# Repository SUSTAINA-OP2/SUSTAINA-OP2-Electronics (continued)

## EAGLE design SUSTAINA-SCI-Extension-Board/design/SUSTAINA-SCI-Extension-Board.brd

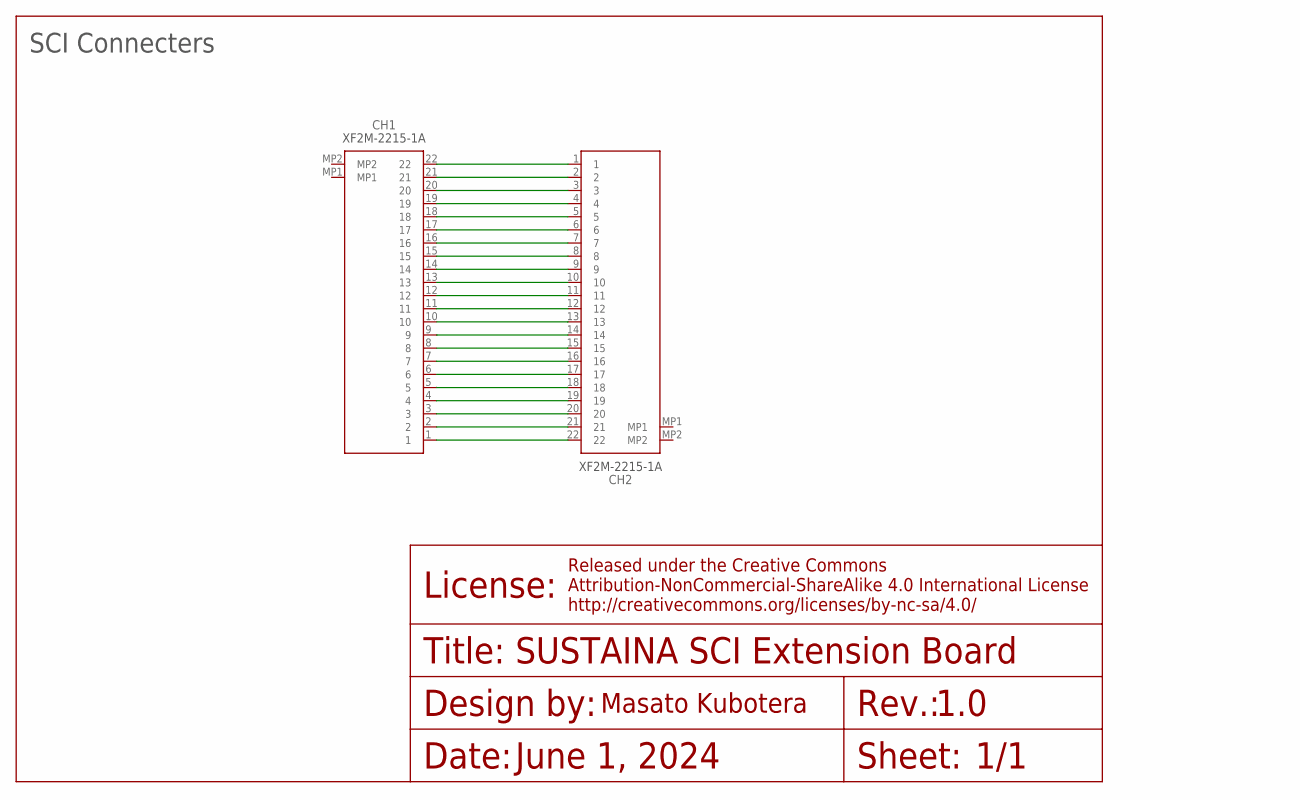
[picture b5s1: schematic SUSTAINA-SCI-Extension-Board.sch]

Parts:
CH1, CH2: XF2M-2215-1A

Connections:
unnamed: CH1.22, CH2.1
unnamed: CH1.21, CH2.2
unnamed: CH1.20, CH2.3
unnamed: CH1.19, CH2.4
unnamed: CH1.18, CH2.5
unnamed: CH1.17, CH2.6
unnamed: CH1.16, CH2.7
unnamed: CH1.15, CH2.8
unnamed: CH1.14, CH2.9
unnamed: CH1.13, CH2.10
unnamed: CH1.12, CH2.11
unnamed: CH1.11, CH2.12
unnamed: CH1.10, CH2.13
unnamed: CH1.9, CH2.14
unnamed: CH1.8, CH2.15
unnamed: CH1.7, CH2.16
unnamed: CH1.6, CH2.17
unnamed: CH1.5, CH2.18
unnamed: CH1.4, CH2.19
unnamed: CH1.2, CH2.21
unnamed: CH1.3, CH2.20
unnamed: CH1.1, CH2.22

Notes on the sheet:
June 1, 2024
SUSTAINA SCI Extension Board
1.0
1/1
SCI Connecters

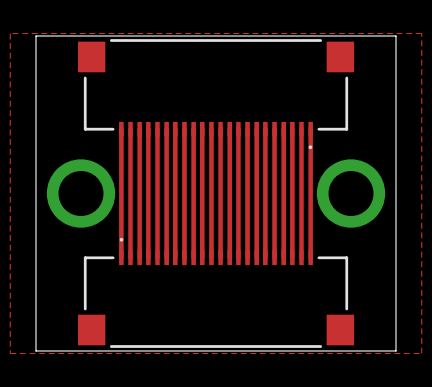
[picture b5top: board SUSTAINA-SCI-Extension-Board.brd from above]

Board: 2 copper layers, 20.0 x 17.5 mm, 4 parts (2 on the bottom side), 22 nets.

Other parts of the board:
U$1: SUSTAINA_SCI_EXTENSION_BOARD-0.03
U$2: DESIGNED_BY_MASATO_KUBOTERA_ON_JUNE_1-0.03

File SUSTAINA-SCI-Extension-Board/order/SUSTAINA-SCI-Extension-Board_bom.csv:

Comment,Designator,Footprint,LCSC Part #
XF2M-2215-1A,CH1 CH2,XF2M-2215-1A,C231416

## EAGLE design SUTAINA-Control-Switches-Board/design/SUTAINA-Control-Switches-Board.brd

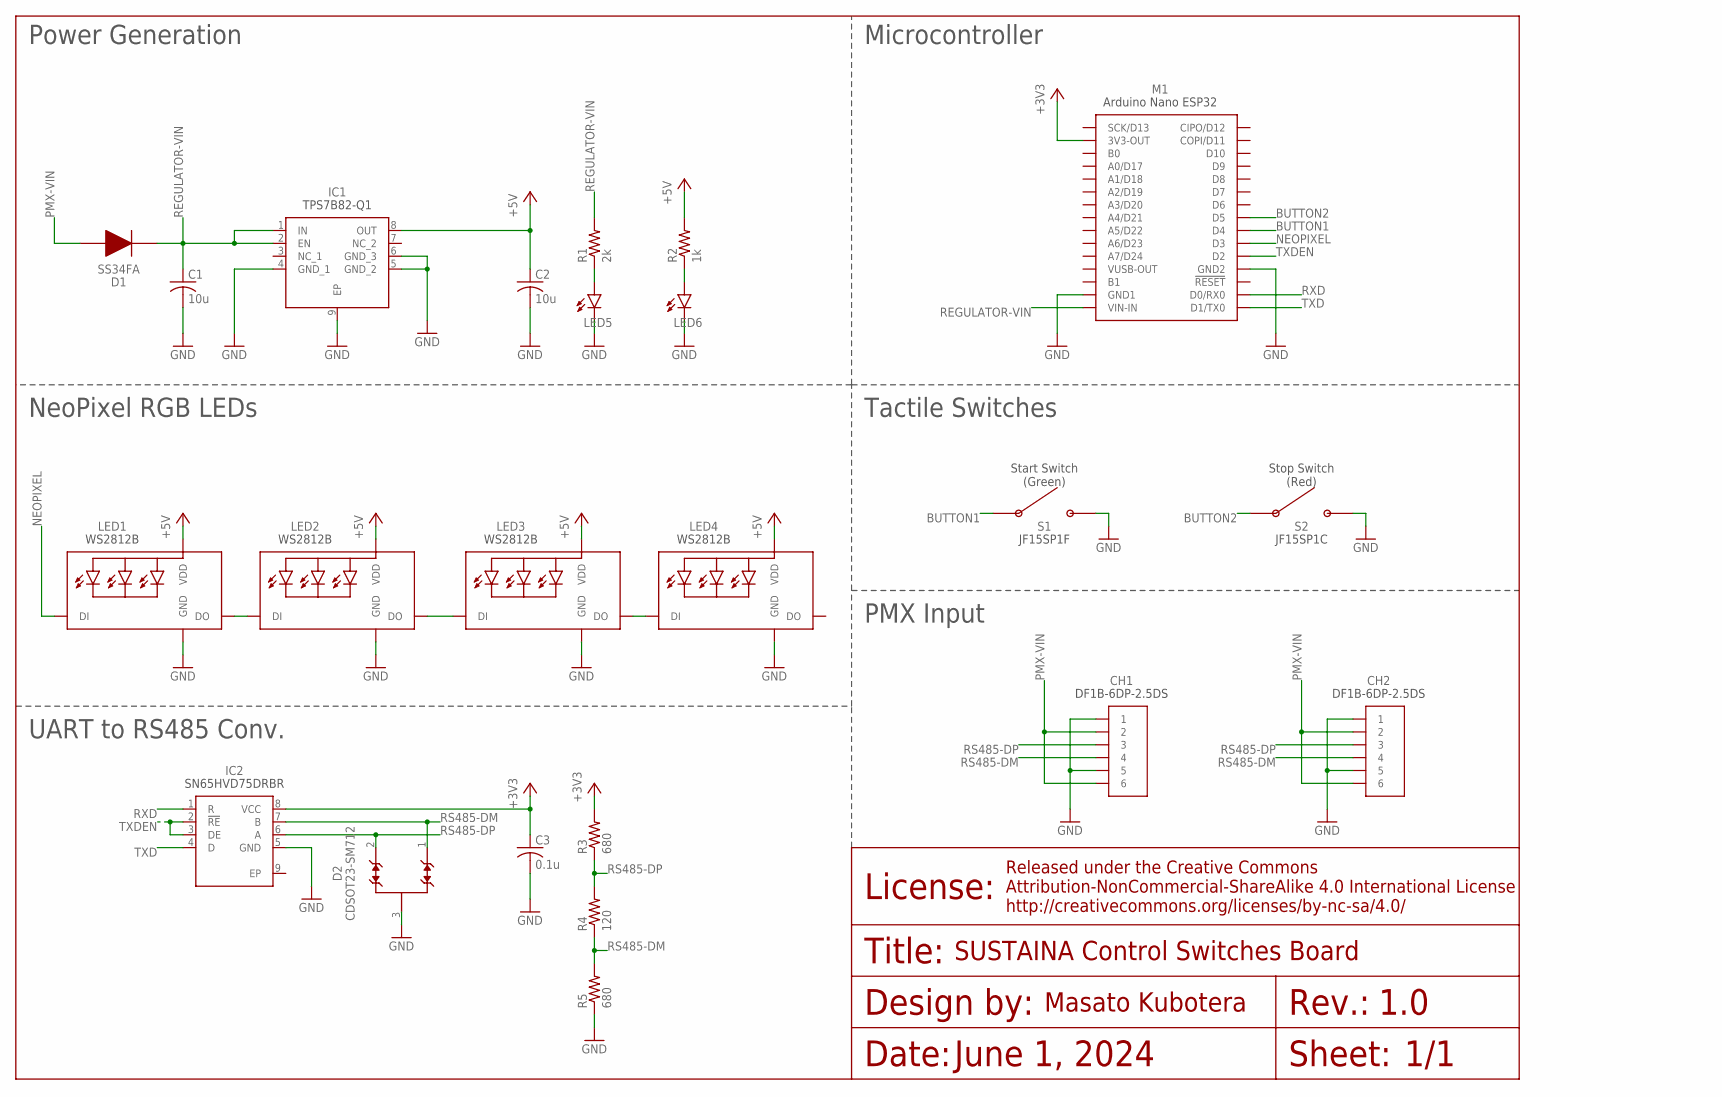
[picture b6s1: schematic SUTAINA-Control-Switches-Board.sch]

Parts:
C1, C2: 10u; C0603
C3: 0.1u; C0603
CH1, CH2: DF1B-6DP-2.5DS
D1: SS34FA
D2: CDSOT23-SM712; SOT-23-3
IC1: TPS7B82-Q1; SOP65P490X110-9N
IC2: SN65HVD75DRBR; SON65P300X300X100-9N
LED1, LED2, LED3, LED4: WS2812B
LED5, LED6: LEDSML0603; SML0603
M1: NANO-ESP32
R1: 2k; R0603
R2: 1k; R0603
R3, R5: 680; R0603
R4: 120; R0603
S1: JF15SP1F; JF15SP1
S2: JF15SP1C; JF15SP1

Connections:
+3V3: C3.1, IC2.8 (VCC), M1.3V3-OUT, R3.2
+5V: C2.1, IC1.8 (OUT), LED1.1-VDD (VDD), LED2.1-VDD (VDD), LED3.1-VDD (VDD), LED4.1-VDD (VDD), R2.2
BUTTON1: M1.D4, S1.1, S1.2
BUTTON2: M1.D5, S2.1, S2.2
DO-DI-1: LED1.2-DOUT (DO), LED2.4-DIN (DI)
DO-DI-2: LED2.2-DOUT (DO), LED3.4-DIN (DI)
DO-DI-3: LED3.2-DOUT (DO), LED4.4-DIN (DI)
GND: C1.2, C2.2, C3.2, CH1.1, CH1.5, CH2.1, CH2.5, D2.3, IC1.4 (GND_1), IC1.5 (GND_2), IC1.6 (GND_3), IC1.9 (EP), IC2.5 (GND), LED1.3-GND (GND), LED2.3-GND (GND), LED3.3-GND (GND), LED4.3-GND (GND), LED5.C, LED6.C, M1.GND1, M1.GND2, R5.1, S1.3, S1.4, S2.3, S2.4
LED-D-RX: LED6.A, R2.1
LED-D-TX: LED5.A, R1.1
NEOPIXEL: LED1.4-DIN (DI), M1.D3
PMX-VIN: CH1.2, CH1.6, CH2.2, CH2.6, D1.2
REGULATOR-VIN: C1.1, D1.1, IC1.1 (IN), IC1.2 (EN), M1.VIN-IN, R1.2
RS485-DM: CH1.4, CH2.4, D2.1, IC2.7 (B), R4.1, R5.2
RS485-DP: CH1.3, CH2.3, D2.2, IC2.6 (A), R3.1, R4.2
RXD: IC2.1 (R), M1.D0/RX0
TXD: IC2.4 (D), M1.D1/TX0
TXDEN: IC2.2 (!RE), IC2.3 (DE), M1.D2

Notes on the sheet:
Start Switch (Green)
Stop Switch (Red)
Tactile Switches
1.0
1/1
June 1, 2024
SUSTAINA Control Switches Board
Power Generation
Microcontroller
NeoPixel RGB LEDs
PMX Input
UART to RS485 Conv.

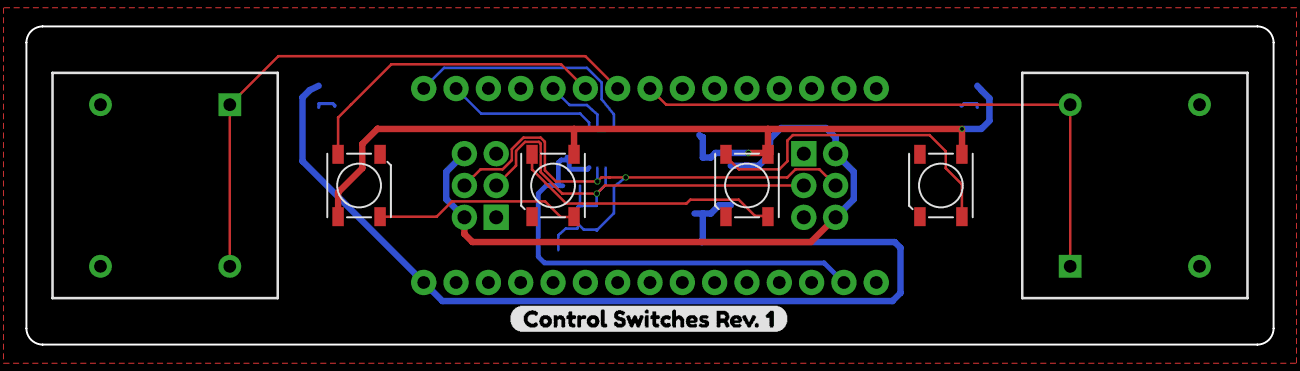
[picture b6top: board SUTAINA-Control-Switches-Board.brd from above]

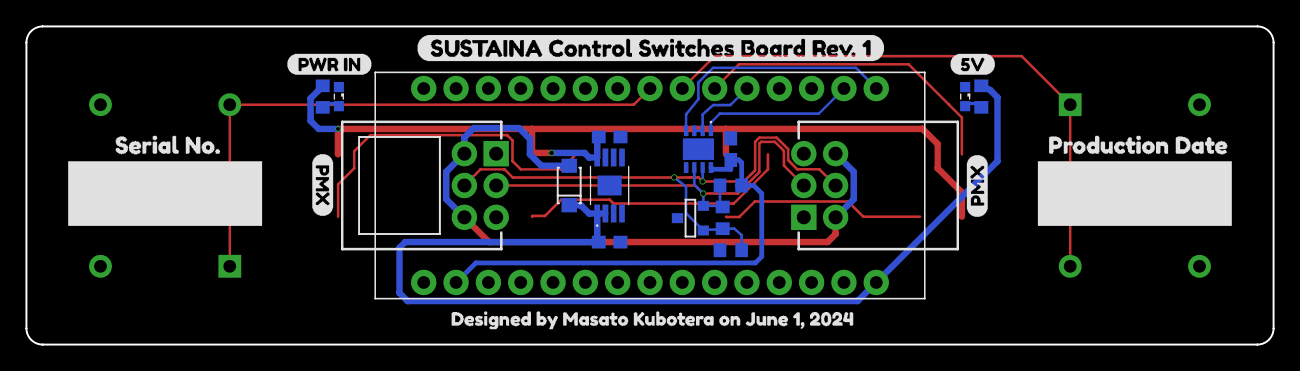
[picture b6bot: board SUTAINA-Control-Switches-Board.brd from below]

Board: 2 copper layers, 98.0 x 25.0 mm, 32 parts (25 on the bottom side), 18 nets.

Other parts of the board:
U$1: SUSTAINA_CONTROL_SWITCHES_BOARD_REV#_10
U$2, U$5: PMX0
U$3: PRODUCTION_DATE0
U$4: SERIAL_NO#0
U$6: CONTROL_SWITCHES_REV#_10
U$7: PWR_IN0
U$8: 5V
U$28: DESIGNED_BY_MASATO_KUBOTERA_ON_FEBRUARY_190DESIGN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; DESIGNED_BY_MASATO_KUBOTERA_ON_JUNE_1

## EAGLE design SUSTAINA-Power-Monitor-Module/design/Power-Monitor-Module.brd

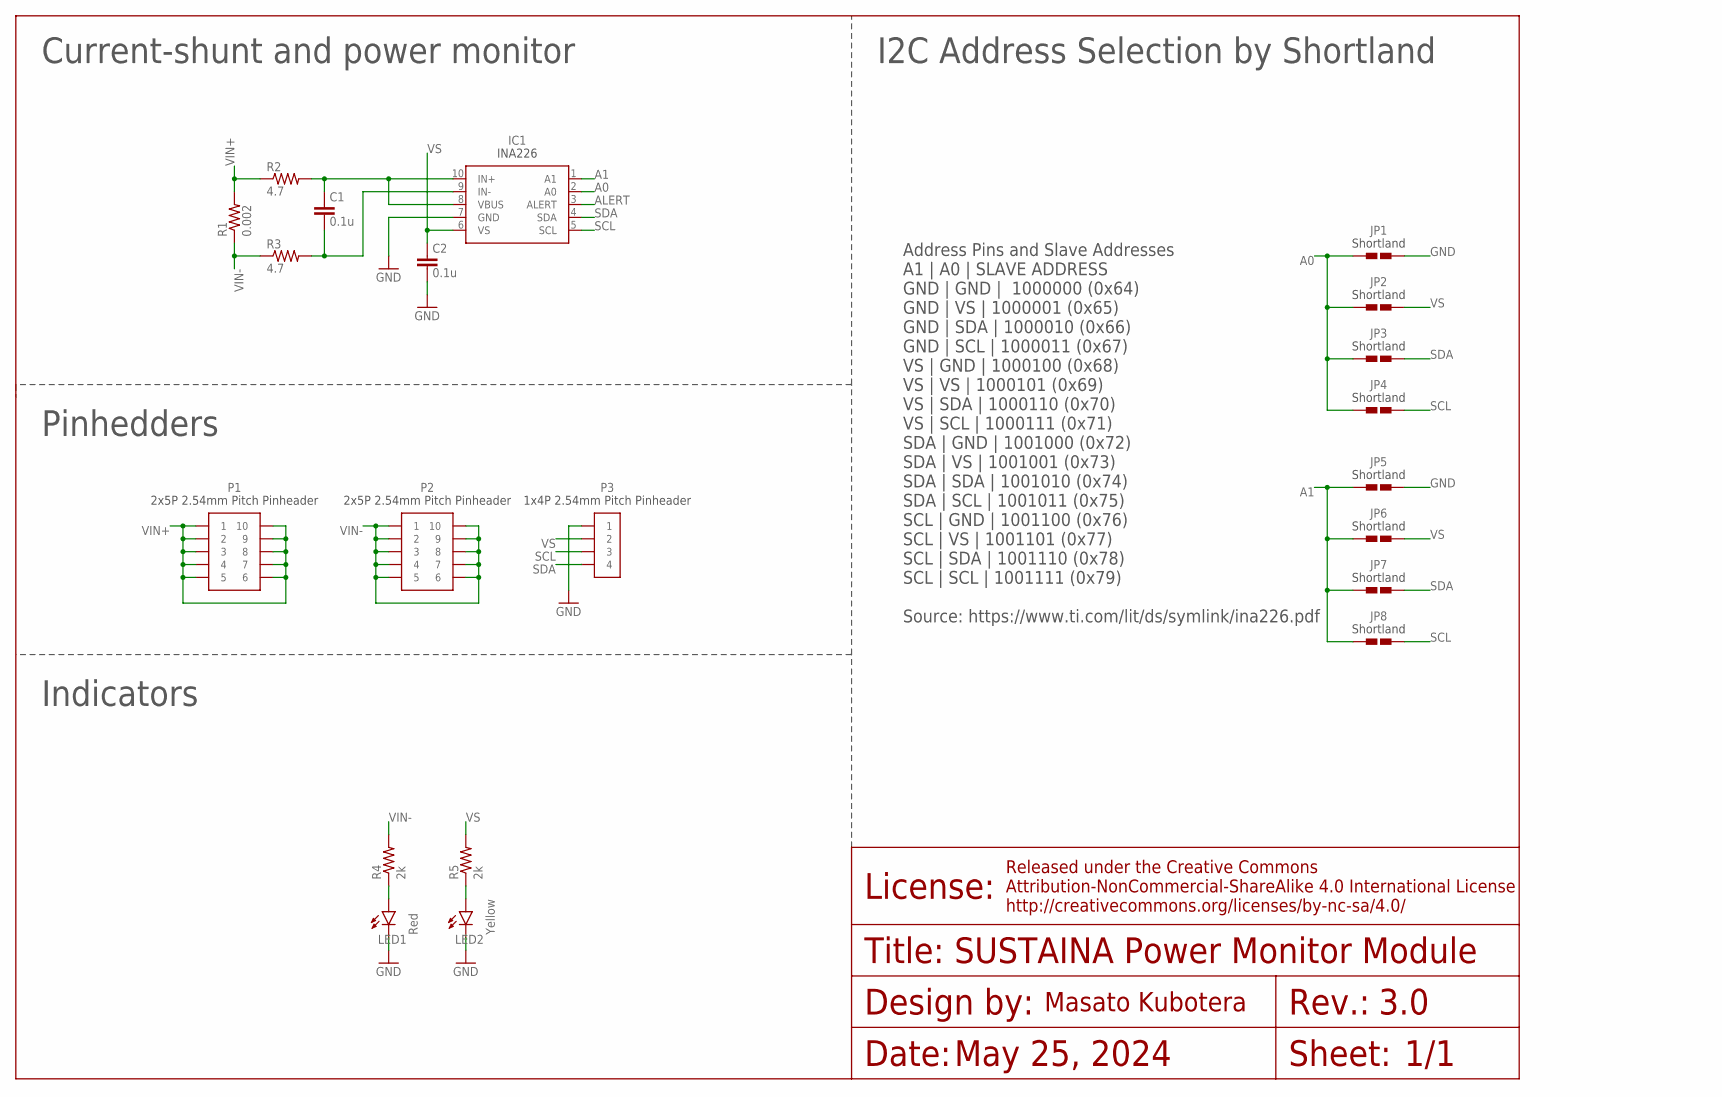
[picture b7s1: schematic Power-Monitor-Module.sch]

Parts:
C1, C2: 0.1u; C0402
IC1: INA226; MSOP-10
JP1, JP2, JP3, JP4, JP5, JP6, JP7, JP8: SHORTLAND
LED1: Red; SML0603
LED2: Yellow; SML0603
P1, P2: 2X5P
P3: 1X4P
R1: 0.002; R2512
R2, R3: 4.7; R0402
R4, R5: 2k; R0402

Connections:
A0: IC1.2 (A0), JP1.1, JP2.1, JP3.1, JP4.1
A1: IC1.1 (A1), JP5.1, JP6.1, JP7.1, JP8.1
ALERT: IC1.3 (ALERT)
GND: C2.2, IC1.7 (GND), JP1.2, JP5.2, LED1.C, LED2.C, P3.1
IN+: C1.1, IC1.8 (VBUS), IC1.10 (IN+), R2.2
IN-: C1.2, IC1.9 (IN-), R3.2
LED1_: LED1.A, R4.1
LED2: LED2.A, R5.1
SCL: IC1.5 (SCL), JP4.2, JP8.2, P3.3
SDA: IC1.4 (SDA), JP3.2, JP7.2, P3.4
VIN+: P1.1, P1.2, P1.3, P1.4, P1.5, P1.6, P1.7, P1.8, P1.9, P1.10, R1.2, R2.1
VIN-: P2.1, P2.2, P2.3, P2.4, P2.5, P2.6, P2.7, P2.8, P2.9, P2.10, R1.1, R3.1, R4.2
VS: C2.1, IC1.6 (VS), JP2.2, JP6.2, P3.2, R5.2

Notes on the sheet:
I2C Address Selection by Shortland
Pinhedders
Current-shunt and power monitor
May 25, 2024
SUSTAINA Power Monitor Module
3.0
1/1
Address Pins and Slave Addresses A1 | A0 | SLAVE ADDRESS GND | GND | 1000000 (0x64) GND | VS | 1000001 (0x65) GND | SDA | 1000010 (0x66) GND | SCL | 1000011 (0x67) VS | GND | 1000100 (0x68) VS | VS | 1000101 (0x69) VS | SDA | 1000110 (0x70) VS | SCL | 1000111 (0x71) SDA | GND | 1001000 (0x72) SDA |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
Indicators

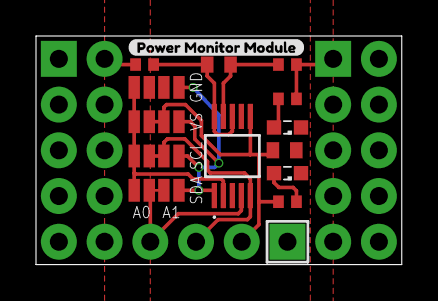
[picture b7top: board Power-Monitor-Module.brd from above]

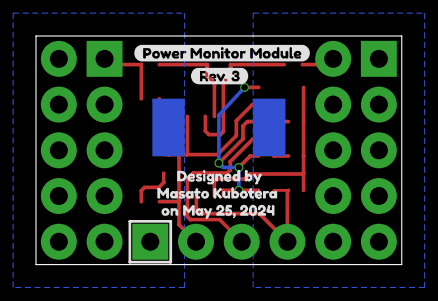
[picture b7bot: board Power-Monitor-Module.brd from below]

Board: 2 copper layers, 20.3 x 12.7 mm, 25 parts (4 on the bottom side), 12 nets.

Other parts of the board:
U$1, U$2: POWER_MONITOR_MODULE
U$3: REV#_3
U$5: DESIGNED_BY_MASATO_KUBOTERA_ON_MAY_25-0.0225

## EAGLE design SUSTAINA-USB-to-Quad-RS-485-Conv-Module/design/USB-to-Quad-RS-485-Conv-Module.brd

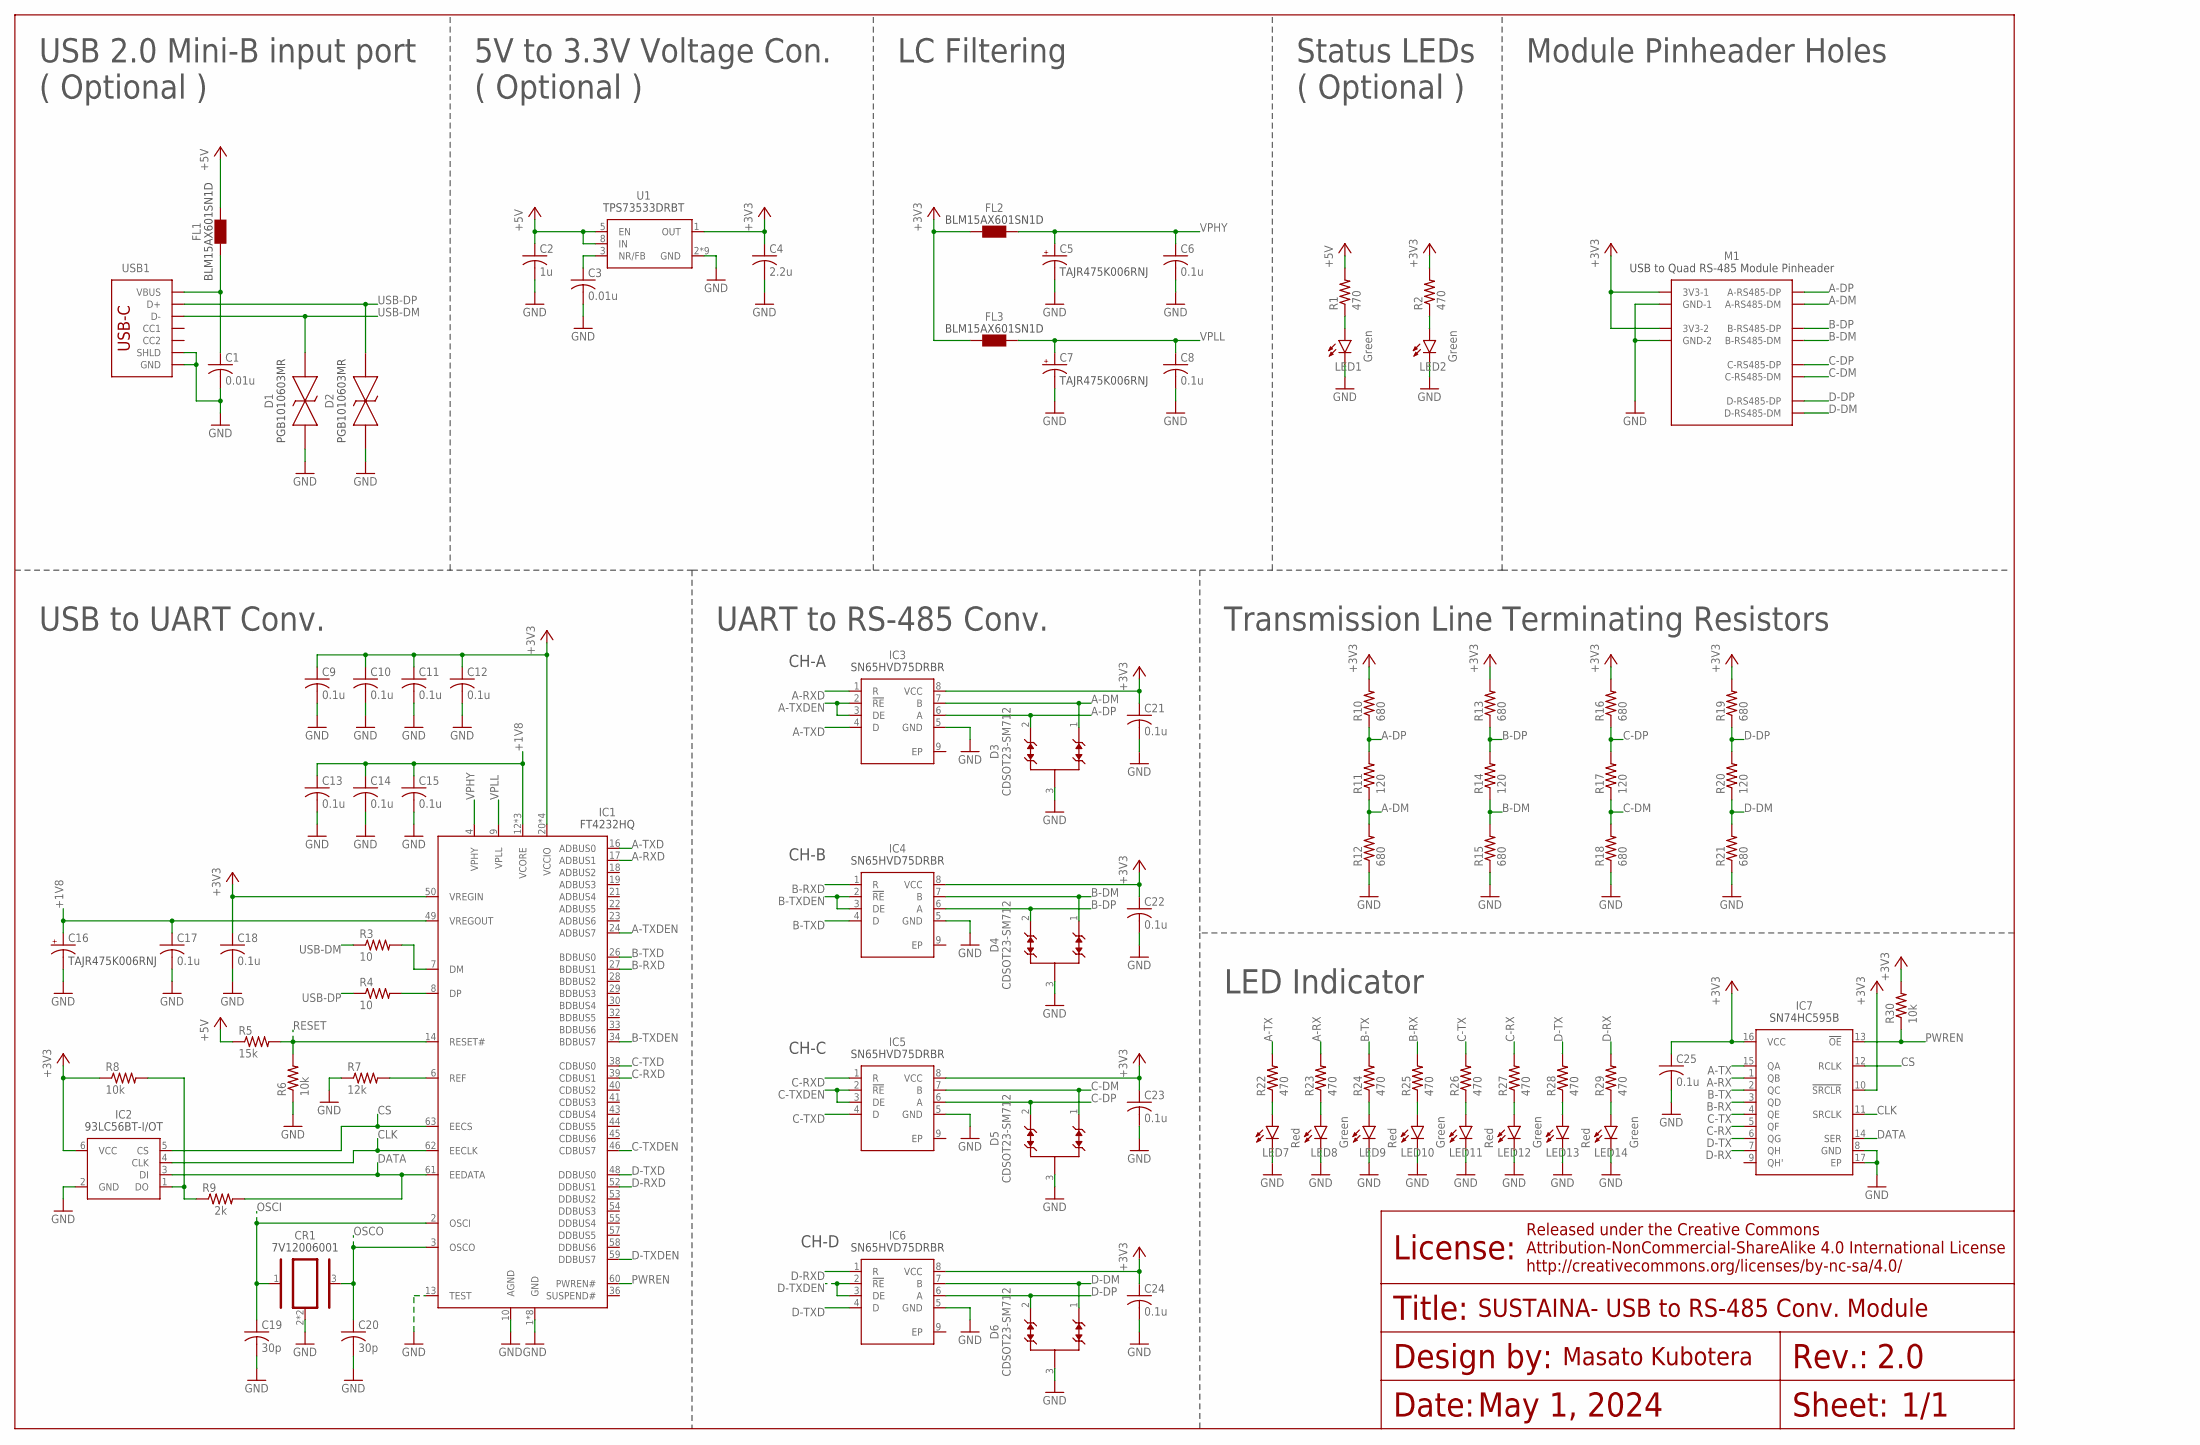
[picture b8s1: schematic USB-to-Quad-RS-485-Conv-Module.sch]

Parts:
C1, C3: 0.01u; C0402
C2: 1u; C0402
C4: 2.2u; C0402
C5, C7, C16: 4.7u; 0805K
C6, C8, C9, C10, C11, C12, C13, C14, C15, C17, C18, C21, C22, C23, C24, C25: 0.1u; C0402
C19, C20: 30p; C0402
CR1: 7V12006001
D1, D2: PGB1010603MR; 0603
D3, D4, D5, D6: CDSOT23-SM712; SOT-23-3
FL1, FL2, FL3: BLM15AX601SN1D
IC1: FT4232HQ
IC2: 93LC56BT-I/OT; SOT-23-6
IC3, IC4, IC5, IC6: SN65HVD75DRBR; SON65P300X300X100-9N
IC7: SN74HC595B; QFN40P250X250X50-17N
LED1, LED2, LED8, LED10, LED12, LED14: Green; SML0603
LED7, LED9, LED11, LED13: Red; SML0603
M1: USB-TO-QUAD-RS-485-CONV-MODULEDIMENSION; USB-TO-QUAD-RS-485-CONV-MODULE-DIMENSION
R1, R2, R22, R23, R24, R25, R26, R27, R28, R29: 470; R0402
R3, R4: 10; R0402
R5: 15k; R0402
R6, R8, R30: 10k; R0402
R7: 12k; R0402
R9: 2k; R0402
R10, R12, R13, R15, R16, R18, R19, R21: 680; R0402
R11, R14, R17, R20: 120; R0402
U1: TPS73533DRBT; SON-8
USB1: USB-C-2.0

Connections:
+1V8: C13.1, C14.1, C15.1, C16.1 (+), C17.1, IC1.12 (VCORE), IC1.37 (VCORE), IC1.49 (VREGOUT), IC1.64 (VCORE)
+3V3: C4.1, C9.1, C10.1, C11.1, C12.1, C18.1, C21.1, C22.1, C23.1, C24.1, C25.1, FL2.1, FL3.1, IC1.20 (VCCIO), IC1.31 (VCCIO), IC1.42 (VCCIO), IC1.50 (VREGIN), IC1.56 (VCCIO), IC2.6 (VCC), IC3.8 (VCC), IC4.8 (VCC), IC5.8 (VCC), IC6.8 (VCC), IC7.10 (!SRCLR), IC7.16 (VCC), M1.3V3-1, M1.3V3-2, R2.2, R8.1, R10.2, R13.2, R16.2, R19.2, R30.2, U1.1 (OUT)
+5V: C2.1, FL1.2, R1.2, R5.1, U1.5 (EN), U1.8 (IN)
A-DM: D3.1, IC3.7 (B), M1.A-RS-485-DM (A-RS485-DM), R11.1, R12.2
A-DP: D3.2, IC3.6 (A), M1.A-RS-485-DP (A-RS485-DP), R10.1, R11.2
A-RX: IC7.1 (QB), R23.2
A-RXD: IC1.17 (ADBUS1), IC3.1 (R)
A-TX: IC7.15 (QA), R22.2
A-TXD: IC1.16 (ADBUS0), IC3.4 (D)
A-TXDEN: IC1.24 (ADBUS7), IC3.2 (!RE), IC3.3 (DE)
B-DM: D4.1, IC4.7 (B), M1.B-RS-485-DM (B-RS485-DM), R14.1, R15.2
B-DP: D4.2, IC4.6 (A), M1.B-RS-485-DP (B-RS485-DP), R13.1, R14.2
B-RX: IC7.3 (QD), R25.2
B-RXD: IC1.27 (BDBUS1), IC4.1 (R)
B-TX: IC7.2 (QC), R24.2
B-TXD: IC1.26 (BDBUS0), IC4.4 (D)
B-TXDEN: IC1.34 (BDBUS7), IC4.2 (!RE), IC4.3 (DE)
C-DM: D5.1, IC5.7 (B), M1.C-RS-485-DM (C-RS485-DM), R17.1, R18.2
C-DP: D5.2, IC5.6 (A), M1.C-RS-485-DP (C-RS485-DP), R16.1, R17.2
C-RX: IC7.5 (QF), R27.2
C-RXD: IC1.39 (CDBUS1), IC5.1 (R)
C-TX: IC7.4 (QE), R26.2
C-TXD: IC1.38 (CDBUS0), IC5.4 (D)
C-TXDEN: IC1.46 (CDBUS7), IC5.2 (!RE), IC5.3 (DE)
CLK: IC1.62 (EECLK), IC2.4 (CLK), IC7.11 (SRCLK)
CS: IC1.63 (EECS), IC2.5 (CS), IC7.12 (RCLK)
D-DM: D6.1, IC6.7 (B), M1.D-RS-485-DM (D-RS485-DM), R20.1, R21.2
D-DP: D6.2, IC6.6 (A), M1.D-RS-485-DP (D-RS485-DP), R19.1, R20.2
D-RX: IC7.7 (QH), R29.2
D-RXD: IC1.52 (DDBUS1), IC6.1 (R)
D-TX: IC7.6 (QG), R28.2
D-TXD: IC1.48 (DDBUS0), IC6.4 (D)
D-TXDEN: IC1.59 (DDBUS7), IC6.2 (!RE), IC6.3 (DE)
DATA: IC1.61 (EEDATA), IC2.3 (DI), IC7.14 (SER), R9.2
FT4232H-DM: IC1.7 (DM), R3.2
FT4232H-DP: IC1.8 (DP), R4.2
FT4232H-REF: IC1.6 (REF), R7.2
GND: C1.2, C2.2, C3.2, C4.2, C5.2 (-), C6.2, C7.2 (-), C8.2, C9.2, C10.2, C11.2, C12.2, C13.2, C14.2, C15.2, C16.2 (-), C17.2, C18.2, C19.2, C20.2, C21.2, C22.2, C23.2, C24.2, C25.2, CR1.2, CR1.4, D1.1, D2.1, D3.3, D4.3, D5.3, D6.3, IC1.1 (GND), IC1.5 (GND), IC1.10 (AGND), IC1.11 (GND), IC1.13 (TEST), IC1.15 (GND), IC1.25 (GND), IC1.35 (GND), IC1.47 (GND), IC1.51 (GND), IC2.2 (GND), IC3.5 (GND), IC4.5 (GND), IC5.5 (GND), IC6.5 (GND), IC7.8 (GND), IC7.17 (EP), LED1.C, LED2.C, LED7.C, LED8.C, LED9.C, LED10.C, LED11.C, LED12.C, LED13.C, LED14.C, M1.GND-1, M1.GND-2, R6.1, R7.1, R12.1, R15.1, R18.1, R21.1, U1.2 (GND), U1.4 (GND), U1.6 (GND), U1.7 (GND), U1.9 (GND), U1.10 (GND), U1.11 (GND), U1.12 (GND), U1.13 (GND), USB1.GND, USB1.GND2 (GND), USB1.SHLD1 (SHLD), USB1.SHLD2 (SHLD), USB1.SHLD3 (SHLD), USB1.SHLD4 (SHLD), USB1.SHLD5 (SHLD), USB1.SHLD6 (SHLD), USB1.SHLD7 (SHLD), USB1.SHLD8 (SHLD)
LED-A-RX: LED8.A, R23.1
LED-A-TX: LED7.A, R22.1
LED-B-RX: LED10.A, R25.1
LED-B-TX: LED9.A, R24.1
LED-C-RX: LED12.A, R27.1
LED-C-TX: LED11.A, R26.1
LED-D-RX: LED14.A, R29.1
LED-D-TX: LED13.A, R28.1
LED_3V3: LED2.A, R2.1
LED_5V: LED1.A, R1.1
NR/FB: C3.1, U1.3 (NR/FB)
OSCI: C19.1, CR1.1, IC1.2 (OSCI)
OSCO: C20.1, CR1.3, IC1.3 (OSCO)
PULLUP-DATA: IC2.1 (DO), R8.2, R9.1
PWREN: IC1.60 (PWREN#), IC7.13 (!OE), R30.1
RESET: IC1.14 (RESET#), R5.2, R6.2
USB-DM: D1.2, R3.1, USB1.A7 (D-), USB1.B7 (D-)
USB-DP: D2.2, R4.1, USB1.A6 (D+), USB1.B6 (D+)
VBUS: C1.1, FL1.1, USB1.VBUS1 (VBUS), USB1.VBUS2 (VBUS)
VPHY: C5.1 (+), C6.1, FL2.2, IC1.4 (VPHY)
VPLL: C7.1 (+), C8.1, FL3.2, IC1.9 (VPLL)

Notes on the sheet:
USB to UART Conv.
UART to RS-485 Conv.
CH-A
CH-D
CH-C
CH-B
Transmission Line Terminating Resistors
Module Pinheader Holes
Status LEDs ( Optional )
LC Filtering
5V to 3.3V Voltage Con. ( Optional )
USB 2.0 Mini-B input port ( Optional )
2.0
1/1
May 1, 2024
SUSTAINA- USB to RS-485 Conv. Module
LED Indicator

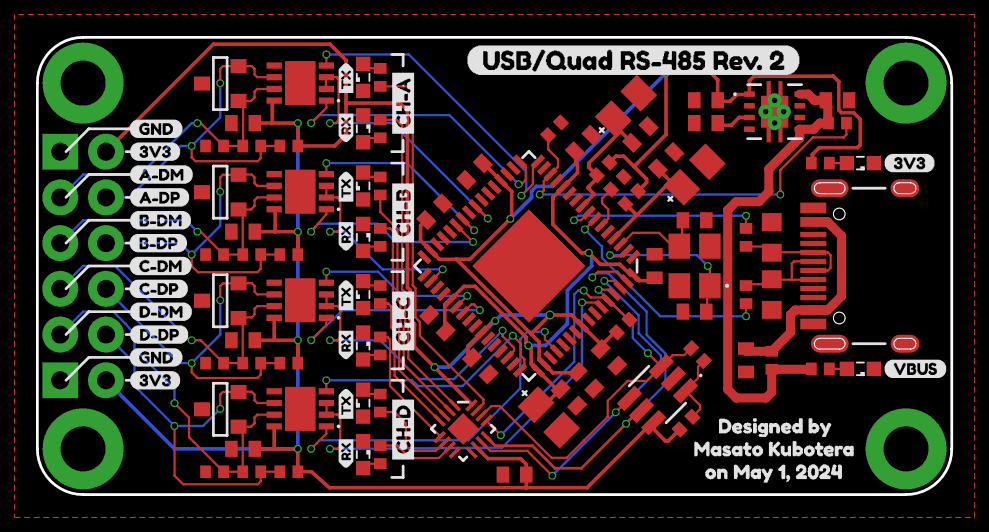
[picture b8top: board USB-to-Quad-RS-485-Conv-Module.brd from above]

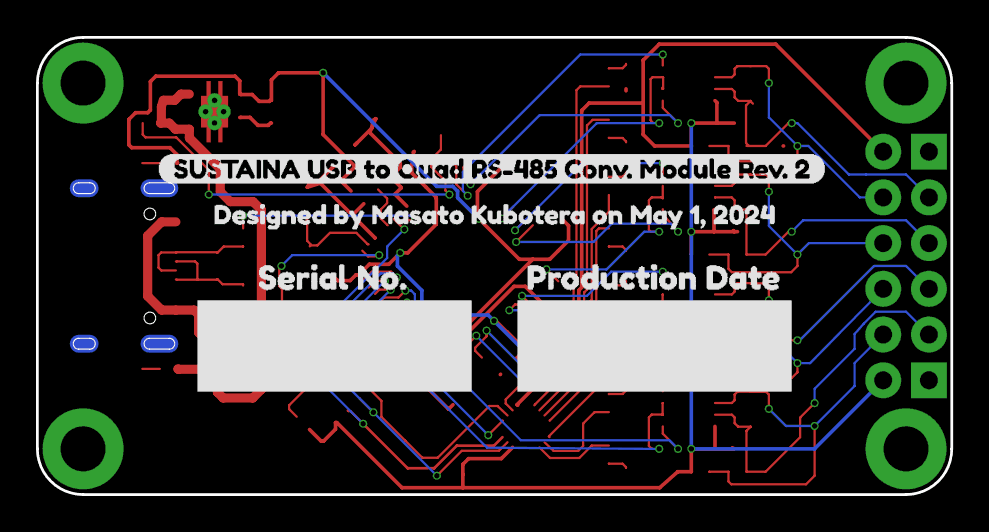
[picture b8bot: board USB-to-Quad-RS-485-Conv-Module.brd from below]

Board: 2 copper layers, 50.8 x 25.4 mm, 117 parts (4 on the bottom side), 59 nets.

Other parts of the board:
U$1: DESIGNED_BY_MASATO_KUBOTERA_ON_MAY_1-COLUMN
U$3: CH#A0
U$4: CH#B0
U$5: CH#C0
U$6: CH#D0
U$7: D-DM-0.025
U$8: D-DP-0.025
U$9: USB#QUAD_RS#485_REV#_2
U$11, U$13, U$15, U$17: RX0
U$12, U$14, U$16, U$18: TX0
U$23, U$24, U$31: 3V3_0.025
U$25, U$26: GND_0.025
U$27: USB_TO_QUAD_RS#485_CONV#_MODULE_REV#_20; SUSTAINA_USB_TO_QUAD_RS#485_CONV#_MODULE_REV#_2
U$28: A-DM-0.025
U$29: PRODUCTION_DATE0
U$30: SERIAL_NO#0
U$32: C-DP-0.025
U$33: DESIGNED_BY_MASATO_KUBOTERA_ON_MAY_1
U$34: A-DP-0.025
U$35: C-DM-0.025
U$36: B-DP-0.025
U$37: B-DM-0.025
U$38: VBUS_0.025

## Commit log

2024-05-02 add LISENSE
2024-05-02 add gitignore
2024-05-02 add PCBs for SUSTAINA-OP2
2024-05-03 add unmanaged file
2024-05-03 deleted the imposition file due to unavailability of the order
2024-05-04 Added connector for DC fans to SUSTAINA-Constant-Voltage-Board
2024-05-28 Corrected the silk printing and via processing method
2024-06-07 Add mass-produced version of Control-Switches-Board
2024-06-07 Add mass-produced version of SCI-Extension-Board
2024-06-07 Add mass-produced version of PMX-Control-Board
2024-06-07 add job file to unmanaged
2024-06-07 Add mass-produced version of Power-Distribution-Board
2024-06-07 Add Power-Logging-Board documentation files
2024-06-07 Add mass-produced version of SBC-Power-Board
2024-06-07 Add StrainGauge-Sensing-Board documentation files
2024-06-07 add pcba image of Power-Monitor-Module
2024-06-07 Add USB-to-Quad-RS-485-Conv-Module documentation files
2024-06-07 Revert Constant-Voltage-Board to version without fan connectors and add data and documentation for outsourcing
2024-06-11 Add mass-produced version of Power-Supply-Switching-Board
2024-06-11 add README.md
2024-06-12 Corrected file paths
2024-06-18 Corrected a via error and added some capacitors
2024-06-24 update images
2024-06-24 Add audio borad
